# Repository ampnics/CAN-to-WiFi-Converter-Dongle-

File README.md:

Overview
This repository contains the PCB design files for a CAN to WiFi converter based on the ESP32. The design allows seamless communication between a Controller Area Network (CAN) bus and WiFi, making it ideal for automotive and IoT applications.

Features

ESP32-based CAN to WiFi bridge

Supports CAN 2.0 communication

Onboard 12V to 5V buck converter for efficient power management

Designed using KiCad
Compact and optimized PCB layout for reliable signal integrity

Project Structure
/schematics/ – KiCad schematic files
/pcb/ – PCB layout files
/gerber/ – Fabrication-ready Gerber files
/bom/ – Bill of Materials (BOM)
/firmware/ – (Optional) ESP32 firmware for CAN-WiFi bridging
Getting Started

Clone the repository:
bash
Copy
Edit
git clone https://github.com/ampnics/CAN-to-WiFi-Converter-Dongle-/
Open the KiCad project files in KiCad v6 or later.
Modify or generate Gerber files for PCB fabrication.
(Optional) Flash the ESP32 firmware for testing.

Requirements

KiCad 6+ for schematic and PCB design
ESP32 Development Environment (if using firmware)
CAN Transceiver Module (e.g., SN65HVD230)

License

This project is licensed under the MIT License – feel free to modify and distribute!

Contributing
Pull requests and improvements are welcome! If you find any issues, feel free to open an issue in the repository.

Author
Developed by Md Ammar Maniyar (@ampnics). Reach out for collaboration or feedback!

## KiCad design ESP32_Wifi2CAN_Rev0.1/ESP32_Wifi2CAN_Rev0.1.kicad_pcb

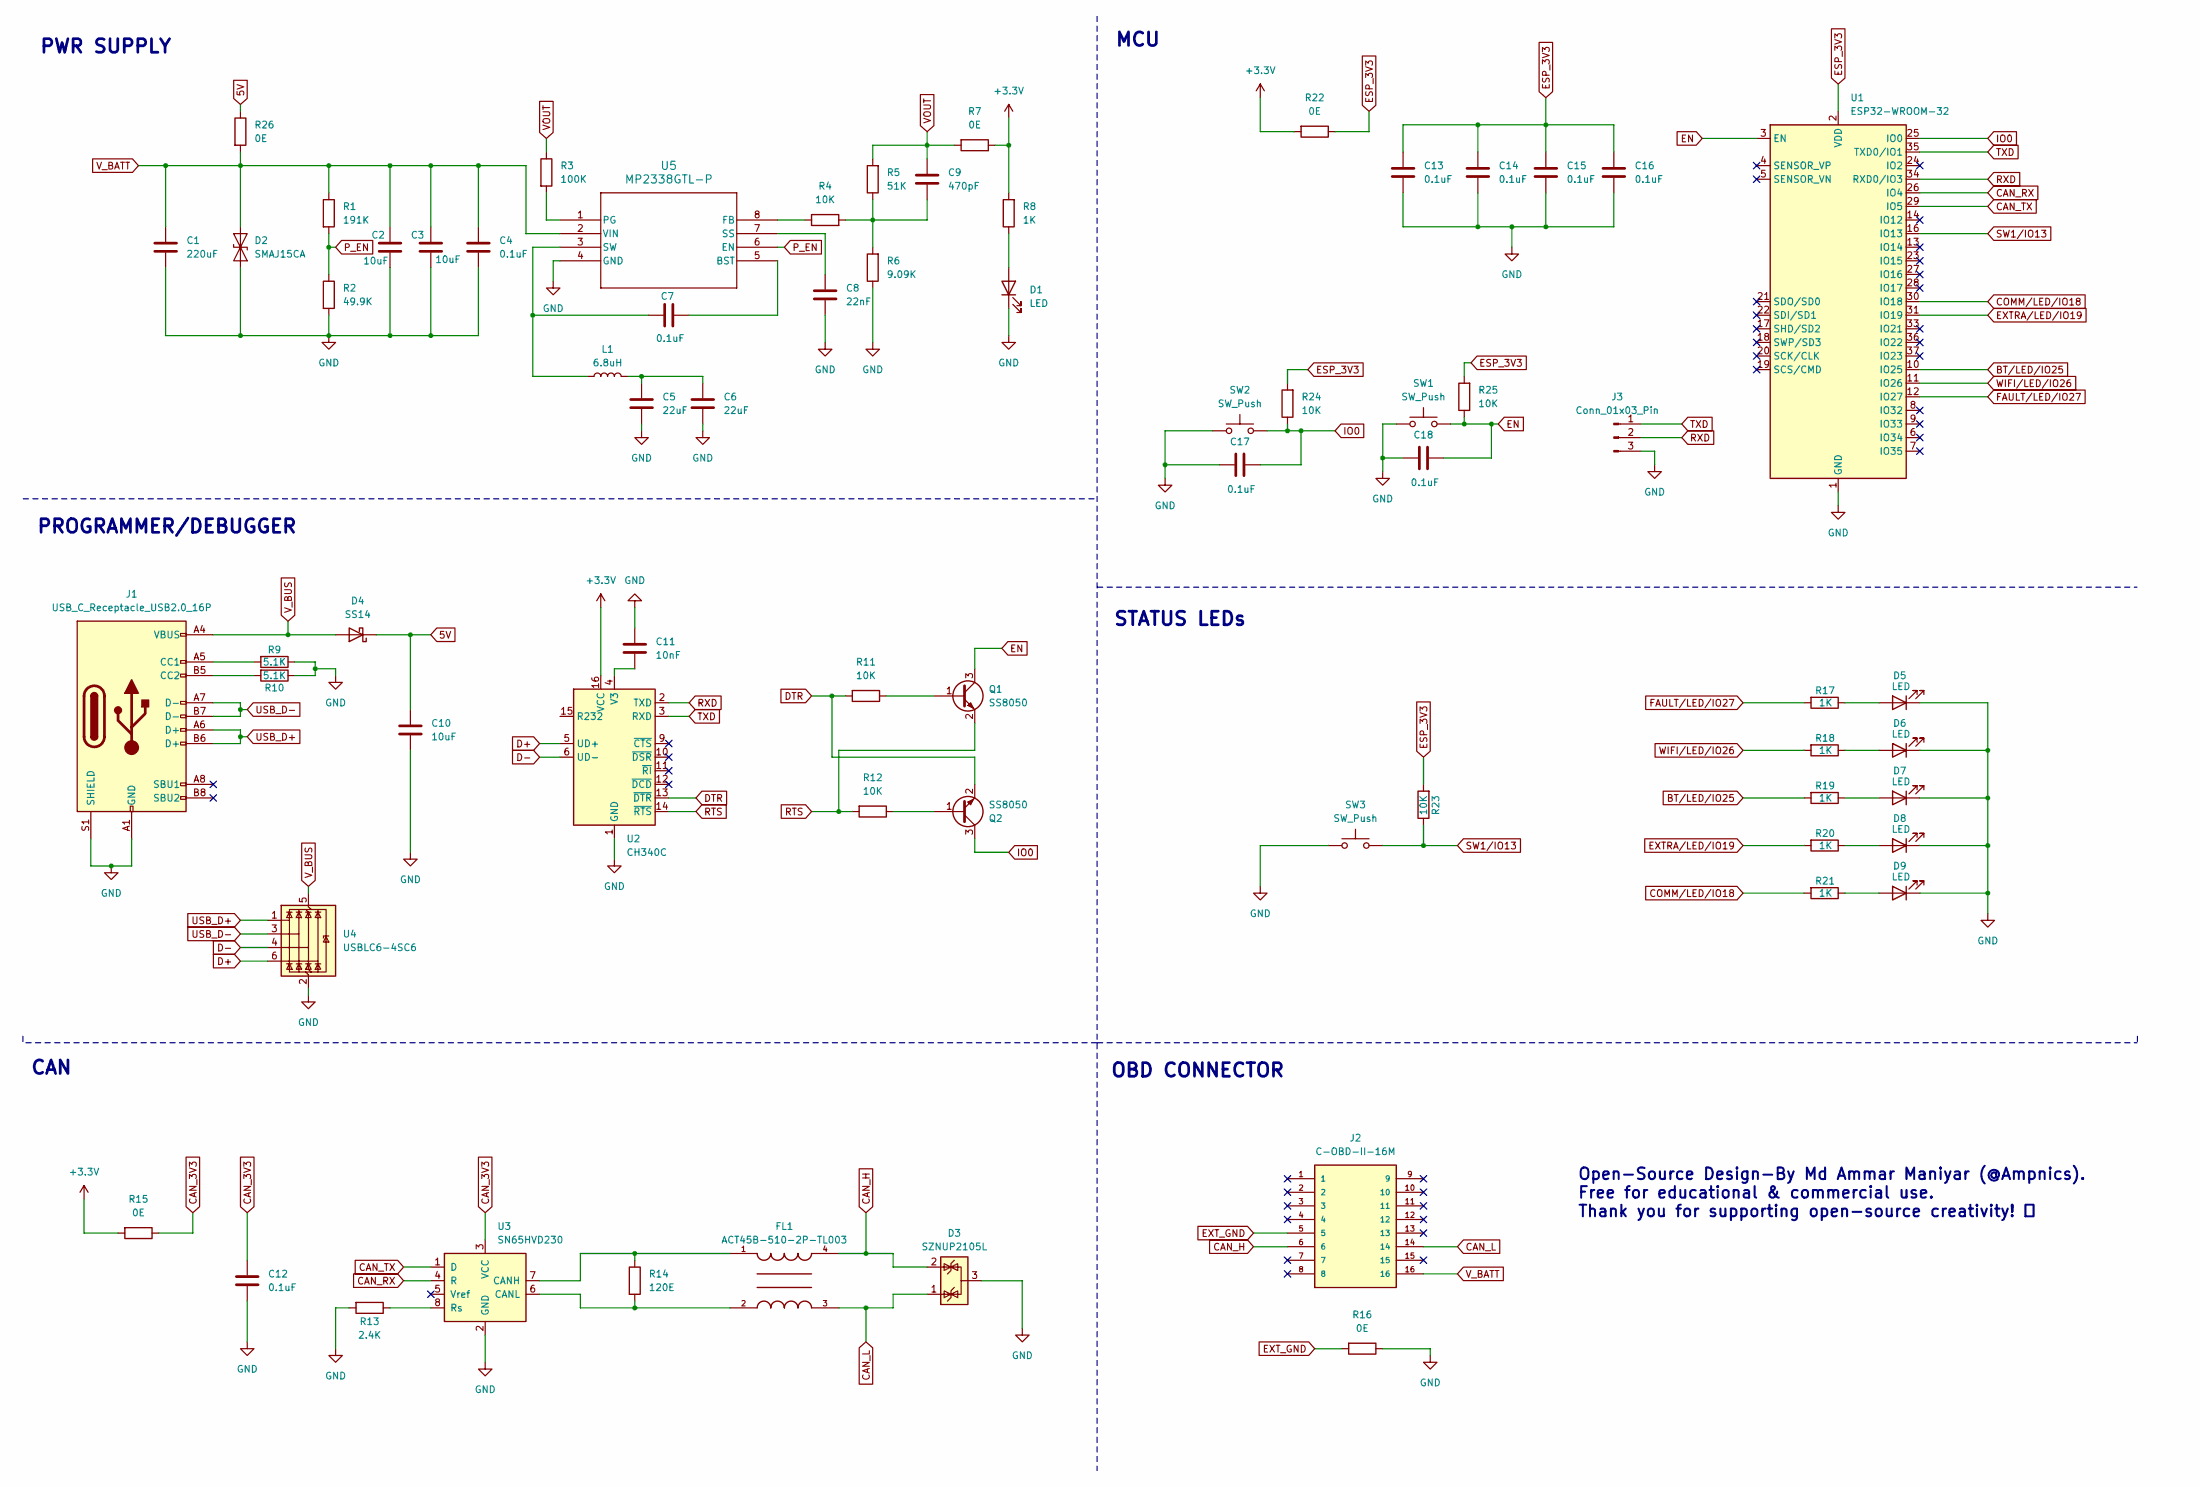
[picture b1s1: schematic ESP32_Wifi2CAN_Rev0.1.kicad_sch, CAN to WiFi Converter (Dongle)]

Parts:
C1: 220uF; C_Elec_8x10.2
C2, C3: 10uF; C_1206_3216Metric
C4, C7, C12, C13, C14, C15, C16, C17, C18: 0.1uF; C_0603_1608Metric
C5, C6: 22uF; C_1206_3216Metric
C8: 22nF; C_0603_1608Metric
C9: 470pF; C_0603_1608Metric
C10: 10uF; C_0603_1608Metric
C11: 10nF; C_0603_1608Metric
D1, D5, D6, D7, D8, D9: LED; LED_0603_1608Metric
D2: SMAJ15CA; D_SMA
D3: SZNUP2105L; SOT-23
D4: SS14; D_SMA
FL1: ACT45B-510-2P-TL003; FIL_ACT45B-510-2P-TL003; PARTREV 20200405
J1: USB_C_Receptacle_USB2.0_16P; USB_C_Receptacle_HRO_TYPE-C-31-M-12
J2: C-OBD-II-16M; COMTECH_C-OBD-II-16M; PARTREV A
J3: Conn_01x03_Pin; PinHeader_1x03_P2.54mm_Vertical
L1: 6.8uH; L_6.3x6.3_H3
Q1, Q2: SS8050; SOT-23
R1: 191K; R_0603_1608Metric
R2: 49.9K; R_0603_1608Metric
R3: 100K; R_0603_1608Metric
R4, R11, R12, R23, R24, R25: 10K; R_0603_1608Metric
R5: 51K; R_0603_1608Metric
R6: 9.09K; R_0603_1608Metric
R7, R15, R16, R22, R26: 0E; R_0603_1608Metric
R8, R17, R18, R19, R20, R21: 1K; R_0603_1608Metric
R9, R10: 5.1K; R_0603_1608Metric
R13: 2.4K; R_0603_1608Metric
R14: 120E; R_0603_1608Metric
SW1, SW2, SW3: SW_Push; SW_Push_SPST_NO_Alps_SKRK
U1: ESP32-WROOM-32
U2: CH340C; SOIC-16_3.9x9.9mm_P1.27mm
U3: SN65HVD230; SOIC-8_3.9x4.9mm_P1.27mm
U4: USBLC6-4SC6; SOT-23-6
U5: MP2338GTL-P; SOT-583-8

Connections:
5V: C10.1, D4.1 (K), R26.1
+3.3V: R7.1, R8.2, R15.2, R22.2, U2.16 (VCC)
BT/LED/IO25: R19.2, U1.10 (IO25)
CAN_3V3: C12.1, R15.1, U3.3 (VCC)
CAN_H: D3.2 (K), FL1.4, J2.6
CAN_L: D3.1 (K), FL1.3, J2.14
CAN_RX: U1.26 (IO4), U3.4 (R)
CAN_TX: U1.29 (IO5), U3.1 (D)
COMM/LED/IO18: R21.2, U1.30 (IO18)
D+: U2.5 (UD+), U4.6 (I/O4)
D-: U2.6 (UD-), U4.4 (I/O3)
DTR: Q2.2 (E), R11.2, U2.13 (~DTR)
EN: C18.2, Q1.3 (C), R25.1, SW1.2, U1.3 (EN)
ESP_3V3: C13.1, C14.1, C15.1, C16.1, R22.1, R23.2, R24.2, R25.2, U1.2 (VDD)
EXTRA/LED/IO19: R20.2, U1.31 (IO19)
EXT_GND: J2.5, R16.2
FAULT/LED/IO27: R17.2, U1.12 (IO27)
GND: C1.2, C2.2, C3.2, C4.2, C5.2, C6.2, C8.2, C10.2, C11.1, C12.2, C13.2, C14.2, C15.2, C16.2, C17.1, C18.1, D1.1 (K), D2.1 (A1), D3.3 (A), D5.1 (K), D6.1 (K), D7.1 (K), D8.1 (K), D9.1 (K), J1.A1 (GND), J1.A12 (GND), J1.B1 (GND), J1.B12 (GND), J1.S1 (SHIELD), J3.3, R2.2, R6.1, R9.1, R10.1, R13.2, R16.1, SW1.1, SW2.1, SW3.1, U1.1 (GND), U1.15 (GND), U1.38 (GND), U1.39 (GND), U2.1 (GND), U3.2 (GND), U4.2 (GND), U5.4 (GND)
IO0: C17.2, Q2.3 (C), R24.1, SW2.2, U1.25 (IO0)
unnamed: C5.1, C6.1, L1.2
unnamed: C9.2, R4.2, R5.1, R6.2
unnamed: D1.2 (A), R8.1
unnamed: D5.2 (A), R17.1
unnamed: D6.2 (A), R18.1
unnamed: D7.2 (A), R19.1
unnamed: D8.2 (A), R20.1
unnamed: D9.2 (A), R21.1
unnamed: J1.A5 (CC1), R9.2
unnamed: J1.B5 (CC2), R10.2
unnamed: Q1.1 (B), R11.1
unnamed: Q2.1 (B), R12.1
unnamed: C11.2, U2.4 (V3)
unnamed: FL1.1, R14.1, U3.7 (CANH)
unnamed: FL1.2, R14.2, U3.6 (CANL)
unnamed: R13.1, U3.8 (Rs)
unnamed: C7.2, U5.5 (BST)
unnamed: R4.1, U5.8 (FB)
unnamed: R3.2, U5.1 (PG)
unnamed: C8.1, U5.7 (SS)
unnamed: C7.1, L1.1, U5.3 (SW)
P_EN: R1.2, R2.1, U5.6 (EN)
RTS: Q1.2 (E), R12.2, U2.14 (~RTS)
RXD: J3.2, U1.34 (RXD0/IO3), U2.2 (TXD)
SW1/IO13: R23.1, SW3.2, U1.16 (IO13)
TXD: J3.1, U1.35 (TXD0/IO1), U2.3 (RXD)
USB_D+: J1.A6 (D+), J1.B6 (D+), U4.1 (I/O1)
USB_D-: J1.A7 (D-), J1.B7 (D-), U4.3 (I/O2)
VOUT: C9.1, R3.1, R5.2, R7.2
V_BATT: C1.1, C2.1, C3.1, C4.1, D2.2 (A2), J2.16, R1.1, R26.2, U5.2 (VIN)
V_BUS: D4.2 (A), J1.A4 (VBUS), J1.A9 (VBUS), J1.B4 (VBUS), J1.B9 (VBUS), U4.5 (VBUS)
WIFI/LED/IO26: R18.2, U1.11 (IO26)

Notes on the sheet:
MCU
STATUS LEDs
OBD CONNECTOR
CAN
Open-Source Design-By Md Ammar Maniyar (@Ampnics). Free for educational & commercial use. Thank you for supporting open-source creativity! 🌟
PWR SUPPLY
PROGRAMMER/DEBUGGER

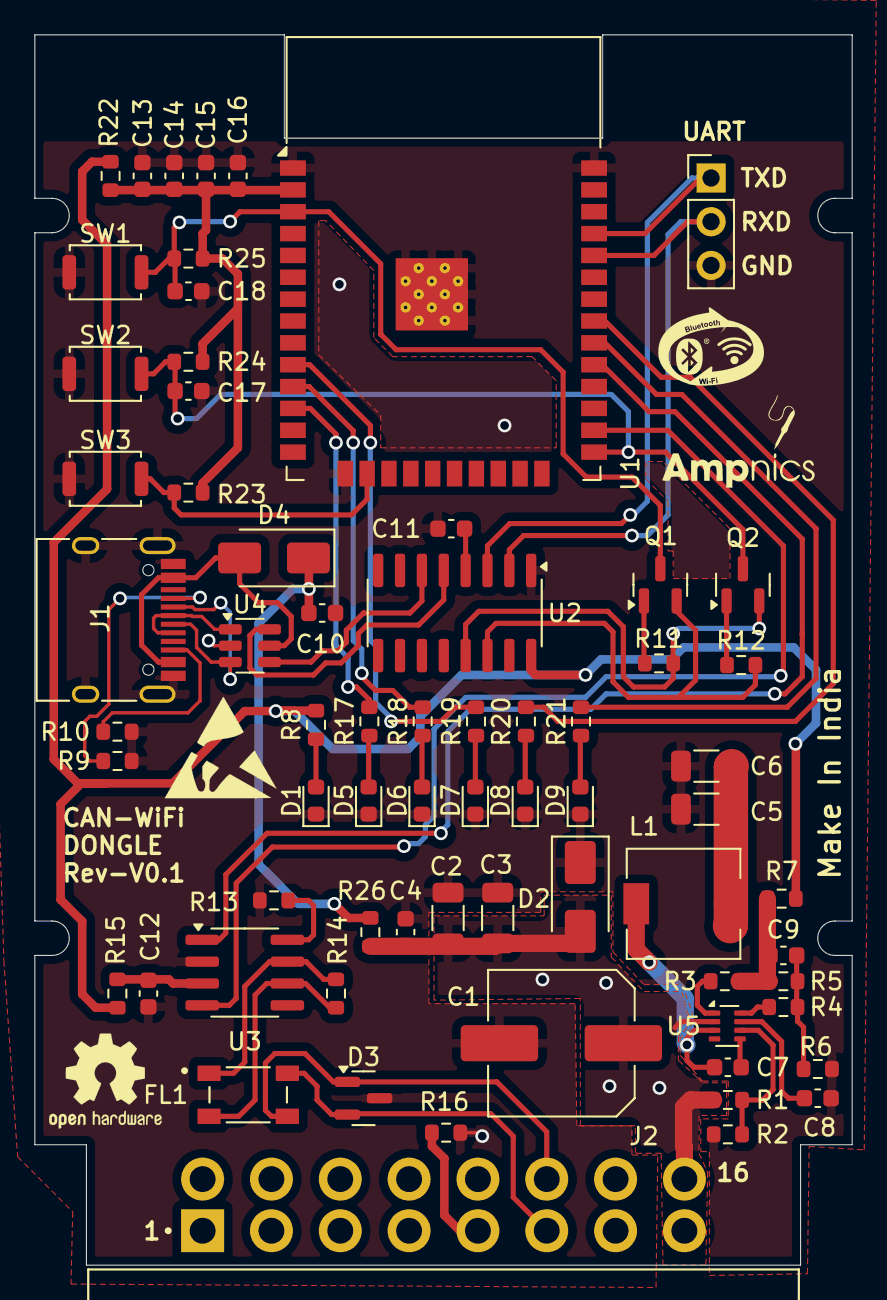
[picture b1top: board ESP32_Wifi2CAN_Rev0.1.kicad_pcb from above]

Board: 2 copper layers, 47.5 x 71.5 mm, 68 parts (0 on the bottom side), 51 nets.

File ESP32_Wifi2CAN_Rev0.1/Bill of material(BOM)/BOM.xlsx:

CAN to WiFI Converter
Reference | Value | Footprint | Qty
C1 | 220uF | Capacitor_SMD:C_Elec_8x10.2 | 1
C2,C3,C10 | 10uF | -- mixed values -- | 3
C4,C7,C12,C13,C14,C15,C16,C17,C18 | 0.1uF | Capacitor_SMD:C_0603_1608Metric | 9
C5,C6 | 22uF | Capacitor_SMD:C_1206_3216Metric | 2
C8 | 22nF | Capacitor_SMD:C_0603_1608Metric | 1
C9 | 470pF | Capacitor_SMD:C_0603_1608Metric | 1
C11 | 10nF | Capacitor_SMD:C_0603_1608Metric | 1
D1,D5,D6,D7,D8,D9 | LED | LED_SMD:LED_0603_1608Metric | 6
D2 | SMAJ15CA | Diode_SMD:D_SMA | 1
D3 | SZNUP2105L | Package_TO_SOT_SMD:SOT-23 | 1
D4 | SS14 | Diode_SMD:D_SMA | 1
FL1 | ACT45B-510-2P-TL003 | ACT45B-510-2P-TL003:FIL_ACT45B-510-2P-TL003 | 1
J1 | USB_C_Receptacle_USB2.0_16P | Connector_USB:USB_C_Receptacle_HRO_TYPE-C-31-M-12 | 1
J2 | C-OBD-II-16M | C-OBD-II-16M:COMTECH_C-OBD-II-16M | 1
J3 | Conn_01x03_Pin | Connector_PinHeader_2.54mm:PinHeader_1x03_P2.54mm_Vertical | 1
L1 | 6.8uH | Inductor_SMD:L_6.3x6.3_H3 | 1
Q1,Q2 | SS8050 | Package_TO_SOT_SMD:SOT-23 | 2
R1 | 191K | Resistor_SMD:R_0603_1608Metric | 1
R2 | 49.9K | Resistor_SMD:R_0603_1608Metric | 1
R3 | 100K | Resistor_SMD:R_0603_1608Metric | 1
R4,R11,R12,R23,R24,R25 | 10K | Resistor_SMD:R_0603_1608Metric | 6
R5 | 51K | Resistor_SMD:R_0603_1608Metric | 1
R6 | 9.09K | Resistor_SMD:R_0603_1608Metric | 1
R7,R15,R16,R22,R26 | 0E | Resistor_SMD:R_0603_1608Metric | 5
R8,R17,R18,R19,R20,R21 | 1K | Resistor_SMD:R_0603_1608Metric | 6
R9,R10 | 5.1K | Resistor_SMD:R_0603_1608Metric | 2
R13 | 2.4K | Resistor_SMD:R_0603_1608Metric | 1
R14 | 120E | Resistor_SMD:R_0603_1608Metric | 1
SW1,SW2,SW3 | SW_Push | Button_Switch_SMD:SW_Push_SPST_NO_Alps_SKRK | 3
U1 | ESP32-WROOM-32 | RF_Module:ESP32-WROOM-32 | 1
U2 | CH340C | Package_SO:SOIC-16_3.9x9.9mm_P1.27mm | 1
U3 | SN65HVD230 | Package_SO:SOIC-8_3.9x4.9mm_P1.27mm | 1
U4 | USBLC6-4SC6 | Package_TO_SOT_SMD:SOT-23-6 | 1
U5 | MP2338GTL-P | Package_TO_SOT_SMD:SOT-583-8 | 1

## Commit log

2025-03-01 README.md
